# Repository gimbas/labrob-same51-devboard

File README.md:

# SAME51-DevBoard

small and simple development board for the same51 mcus

## Built With

* eagle cad

## Contributing

Currently not looking for external contributers.

Please read [CONTRIBUTING.md](//) for details on our code of conduct, and the process for submitting pull requests to us.

## Authors

* **Rafael Silva** - *initial work* - [gimbas](https://github.com/gimbas)

See also the list of [contributors](https://github.com/gimbas/labrob-same51-devboard/graphs/contributors) who participated in this project.

## License

This project is licensed under the CC 3.0 License - see the [LICENSE.md](LICENSE.md) file for details

## Acknowledgments

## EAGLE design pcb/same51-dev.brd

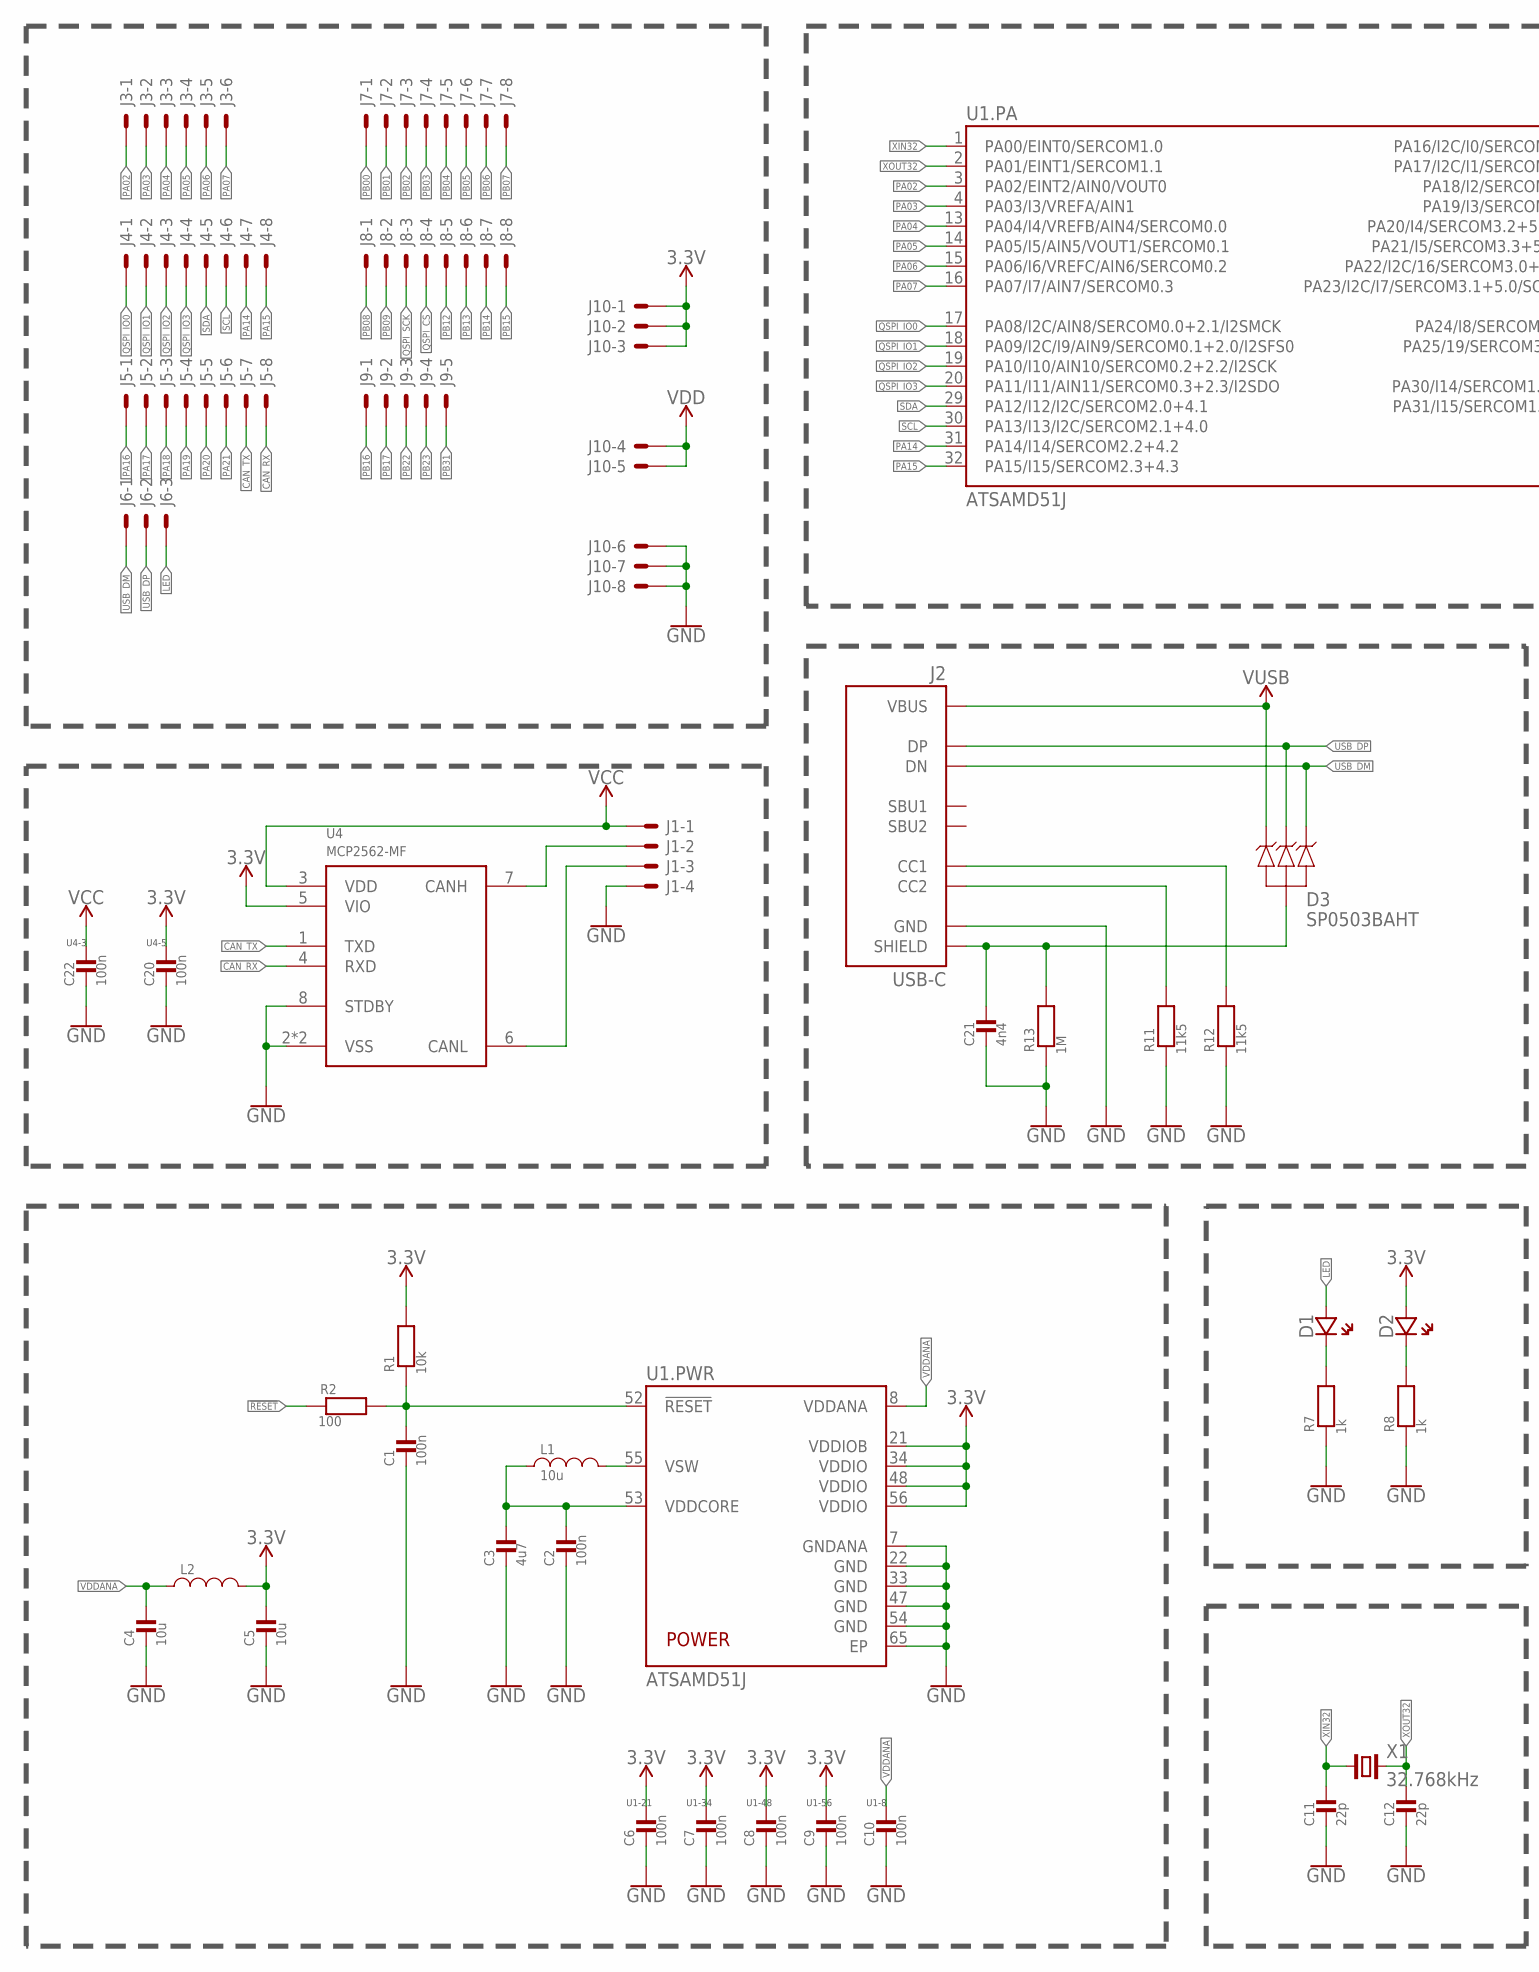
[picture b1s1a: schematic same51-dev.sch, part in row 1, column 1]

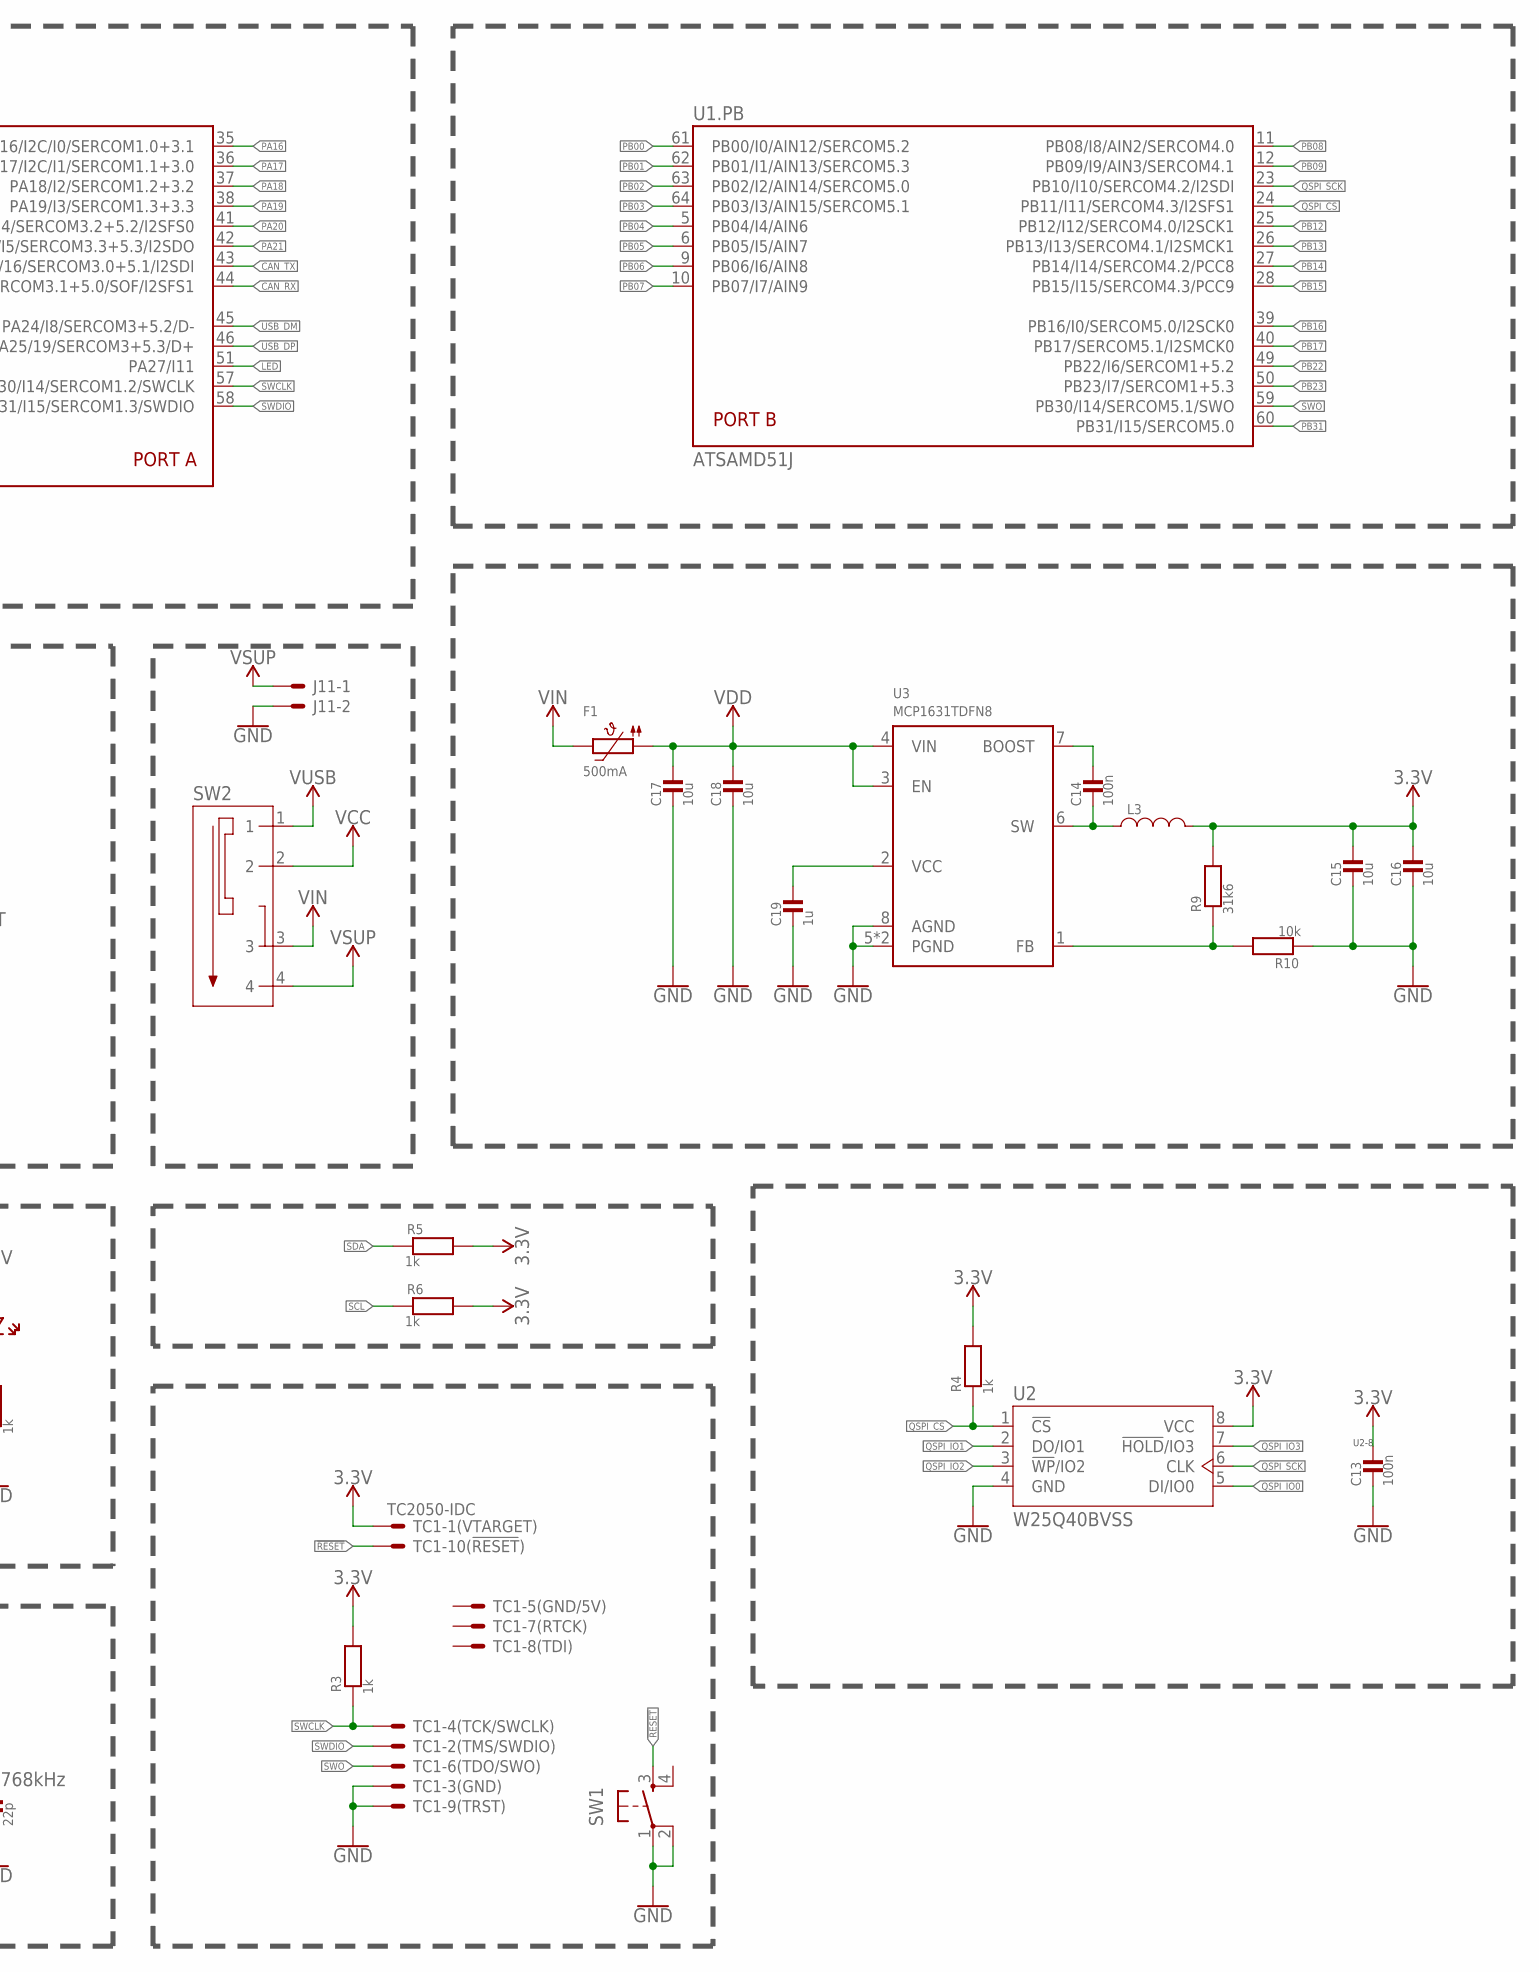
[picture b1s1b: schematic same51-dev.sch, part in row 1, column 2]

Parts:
C1, C2, C6, C7, C8, C9, C10, C13, C14, C20, C22: 100n; 0603_WAVE
C3: 4u7; 0603_WAVE
C4, C5, C15, C16, C17, C18: 10u; 0603_WAVE
C11, C12: 22p; 0603_WAVE
C19: 1u; 0603_WAVE
C21: 4n4; 0603_WAVE
D1, D2: LED0603; CHIPLED_0603
D3: SP0503BAHT; SOT143
F1: 500mA; 0805
J1: 4; 1X4_2.54
J2: USB-C
J3: 6; 1X6_2.54
J4, J5, J7, J8, J10: 8; 1X8_2.54
J6: 3; 1X3_2.54
J9: 5; 1X5_2.54
J11: 2; 2X1_2.54
L1: 10u; _0806
L2: INDUCTOR_NC_0603; _0603
L3: INDUCTOR_NC_0806; _0806
R1, R10: 10k; 0603_WAVE
R2: 100; 0603_WAVE
R3, R4, R5, R6, R7, R8: 1k; 0603_WAVE
R9: 31k6; 0603_WAVE
R11, R12: 11k5; 0603_WAVE
R13: 1M; 0603_WAVE
SW1: PUSH_BUTTON3X4X2; 3X4X2
SW2: MSK-13C01
TC1: TC2050-IDC
U1: ATSAMD51J; VQFN64
U2: W25Q40BVSS; SO08-SS
U3: MCP1631TDFN8; TDFN8
U4: MCP2562-MF; DFN8
X1: 32.768kHz; 2-SMD-3215

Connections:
3.3V: C5.P$1, C6.P$1, C7.P$1, C8.P$1, C9.P$1, C13.P$1, C15.P$1, C16.P$1, C20.P$1, D2.A (AN), J10.1, J10.2, J10.3, L2.2, L3.2, R1.P$2, R3.P$2, R4.P$2, R5.P$2, R6.P$2, R9.P$2, TC1.1, U1.21 (VDDIOB), U1.34 (VDDIO), U1.48 (VDDIO), U1.56 (VDDIO), U2.8 (VCC), U4.5 (VIO)
!RESET: R2.P$1, SW1.3 (4), TC1.10
CAN_RX: J5.8, U1.44 (PA23/I2C/I7/SERCOM3.1+5.0/SOF/I2SFS1), U4.4 (RXD)
CAN_TX: J5.7, U1.43 (PA22/I2C/16/SERCOM3.0+5.1/I2SDI), U4.1 (TXD)
GND: C1.P$2, C2.P$2, C3.P$2, C4.P$2, C5.P$2, C6.P$2, C7.P$2, C8.P$2, C9.P$2, C10.P$2, C11.P$2, C12.P$2, C13.P$2, C15.P$2, C16.P$2, C17.P$2, C18.P$2, C19.P$2, C20.P$2, C21.P$2, C22.P$2, J1.4, J2.A1/B12 (GND), J2.B1/A12 (GND), J10.6, J10.7, J10.8, J11.2, R7.P$1, R8.P$1, R10.P$1, R11.P$1, R12.P$1, R13.P$1, SW1.1, SW1.2, TC1.3, TC1.9, U1.7 (GNDANA), U1.22 (GND), U1.33 (GND), U1.47 (GND), U1.54 (GND), U1.65 (EP), U2.4 (GND), U3.5 (PGND), U3.8 (AGND), U3.9 (PGND), U4.2 (VSS), U4.8 (STDBY), U4.9 (VSS)
LED: D1.A (AN), J6.3, U1.51 (PA27/I11)
unnamed: C1.P$1, R1.P$1, R2.P$2, U1.52 (!RESET)
unnamed: L1.2, U1.55 (VSW)
unnamed: C2.P$1, C3.P$1, L1.1, U1.53 (VDDCORE)
unnamed: C14.P$1, U3.7 (BOOST)
unnamed: C14.P$2, L3.1, U3.6 (SW)
unnamed: R9.P$1, R10.P$2, U3.1 (FB)
unnamed: C19.P$1, U3.2 (VCC)
unnamed: J1.3, U4.6 (CANL)
unnamed: J1.2, U4.7 (CANH)
unnamed: D1.C (CA), R7.P$2
unnamed: C21.P$1, D3.1, J2.SHIELD0 (SHIELD), J2.SHIELD1 (SHIELD), J2.SHIELD2 (SHIELD), J2.SHIELD3 (SHIELD), R13.P$2
unnamed: J2.B5 (CC2), R11.P$2
unnamed: J2.A5 (CC1), R12.P$2
unnamed: D2.C (CA), R8.P$2
PA02: J3.1, U1.3 (PA02/EINT2/AIN0/VOUT0)
PA03: J3.2, U1.4 (PA03/I3/VREFA/AIN1)
PA04: J3.3, U1.13 (PA04/I4/VREFB/AIN4/SERCOM0.0)
PA05: J3.4, U1.14 (PA05/I5/AIN5/VOUT1/SERCOM0.1)
PA06: J3.5, U1.15 (PA06/I6/VREFC/AIN6/SERCOM0.2)
PA07: J3.6, U1.16 (PA07/I7/AIN7/SERCOM0.3)
PA14: J4.7, U1.31 (PA14/I14/SERCOM2.2+4.2)
PA15: J4.8, U1.32 (PA15/I15/SERCOM2.3+4.3)
PA16: J5.1, U1.35 (PA16/I2C/I0/SERCOM1.0+3.1)
PA17: J5.2, U1.36 (PA17/I2C/I1/SERCOM1.1+3.0)
PA18: J5.3, U1.37 (PA18/I2/SERCOM1.2+3.2)
PA19: J5.4, U1.38 (PA19/I3/SERCOM1.3+3.3)
PA20: J5.5, U1.41 (PA20/I4/SERCOM3.2+5.2/I2SFS0)
PA21: J5.6, U1.42 (PA21/I5/SERCOM3.3+5.3/I2SDO)
PB00: J7.1, U1.61 (PB00/I0/AIN12/SERCOM5.2)
PB01: J7.2, U1.62 (PB01/I1/AIN13/SERCOM5.3)
PB02: J7.3, U1.63 (PB02/I2/AIN14/SERCOM5.0)
PB03: J7.4, U1.64 (PB03/I3/AIN15/SERCOM5.1)
PB04: J7.5, U1.5 (PB04/I4/AIN6)
PB05: J7.6, U1.6 (PB05/I5/AIN7)
PB06: J7.7, U1.9 (PB06/I6/AIN8)
PB07: J7.8, U1.10 (PB07/I7/AIN9)
PB08: J8.1, U1.11 (PB08/I8/AIN2/SERCOM4.0)
PB09: J8.2, U1.12 (PB09/I9/AIN3/SERCOM4.1)
PB12: J8.5, U1.25 (PB12/I12/SERCOM4.0/I2SCK1)
PB13: J8.6, U1.26 (PB13/I13/SERCOM4.1/I2SMCK1)
PB14: J8.7, U1.27 (PB14/I14/SERCOM4.2/PCC8)
PB15: J8.8, U1.28 (PB15/I15/SERCOM4.3/PCC9)
PB16: J9.1, U1.39 (PB16/I0/SERCOM5.0/I2SCK0)
PB17: J9.2, U1.40 (PB17/SERCOM5.1/I2SMCK0)
PB22: J9.3, U1.49 (PB22/I6/SERCOM1+5.2)
PB23: J9.4, U1.50 (PB23/I7/SERCOM1+5.3)
PB31: J9.5, U1.60 (PB31/I15/SERCOM5.0)
QSPI_CS: J8.4, R4.P$1, U1.24 (PB11/I11/SERCOM4.3/I2SFS1), U2.1 (!CS!)
QSPI_IO0: J4.1, U1.17 (PA08/I2C/AIN8/SERCOM0.0+2.1/I2SMCK), U2.5 (DI/IO0)
QSPI_IO1: J4.2, U1.18 (PA09/I2C/I9/AIN9/SERCOM0.1+2.0/I2SFS0), U2.2 (DO/IO1)
QSPI_IO2: J4.3, U1.19 (PA10/I10/AIN10/SERCOM0.2+2.2/I2SCK), U2.3 (!WP!/IO2)
QSPI_IO3: J4.4, U1.20 (PA11/I11/AIN11/SERCOM0.3+2.3/I2SDO), U2.7 (!HOLD!/IO3)
QSPI_SCK: J8.3, U1.23 (PB10/I10/SERCOM4.2/I2SDI), U2.6 (CLK)
SCL: J4.6, R6.P$1, U1.30 (PA13/I13/I2C/SERCOM2.1+4.0)
SDA: J4.5, R5.P$1, U1.29 (PA12/I12/I2C/SERCOM2.0+4.1)
SWCLK: R3.P$1, TC1.4, U1.57 (PA30/I14/SERCOM1.2/SWCLK)
SWDIO: TC1.2, U1.58 (PA31/I15/SERCOM1.3/SWDIO)
SWO: TC1.6, U1.59 (PB30/I14/SERCOM5.1/SWO)
USB_DM: D3.4, J2.A7 (DN), J2.B7 (DN), J6.1, U1.45 (PA24/I8/SERCOM3+5.2/D-)
USB_DP: D3.3, J2.A6 (DP), J2.B6 (DP), J6.2, U1.46 (PA25/19/SERCOM3+5.3/D+)
VCC: C22.P$1, J1.1, SW2.2, U4.3 (VDD)
VDD: C17.P$1, C18.P$1, F1.1, J10.4, J10.5, U3.3 (EN), U3.4 (VIN)
VDDANA: C4.P$1, C10.P$1, L2.1, U1.8 (VDDANA)
VIN: F1.2, SW2.3
VSUP: J11.1, SW2.4
VUSB: D3.2, J2.A4/B9 (VBUS), J2.B4/A9 (VBUS), SW2.1
XIN32: C11.P$1, U1.1 (PA00/EINT0/SERCOM1.0), X1.1
XOUT32: C12.P$1, U1.2 (PA01/EINT1/SERCOM1.1), X1.2

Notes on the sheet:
U1-21
U1-34
U1-48
U1-56
U1-8
U2-8
U4-5
U4-3

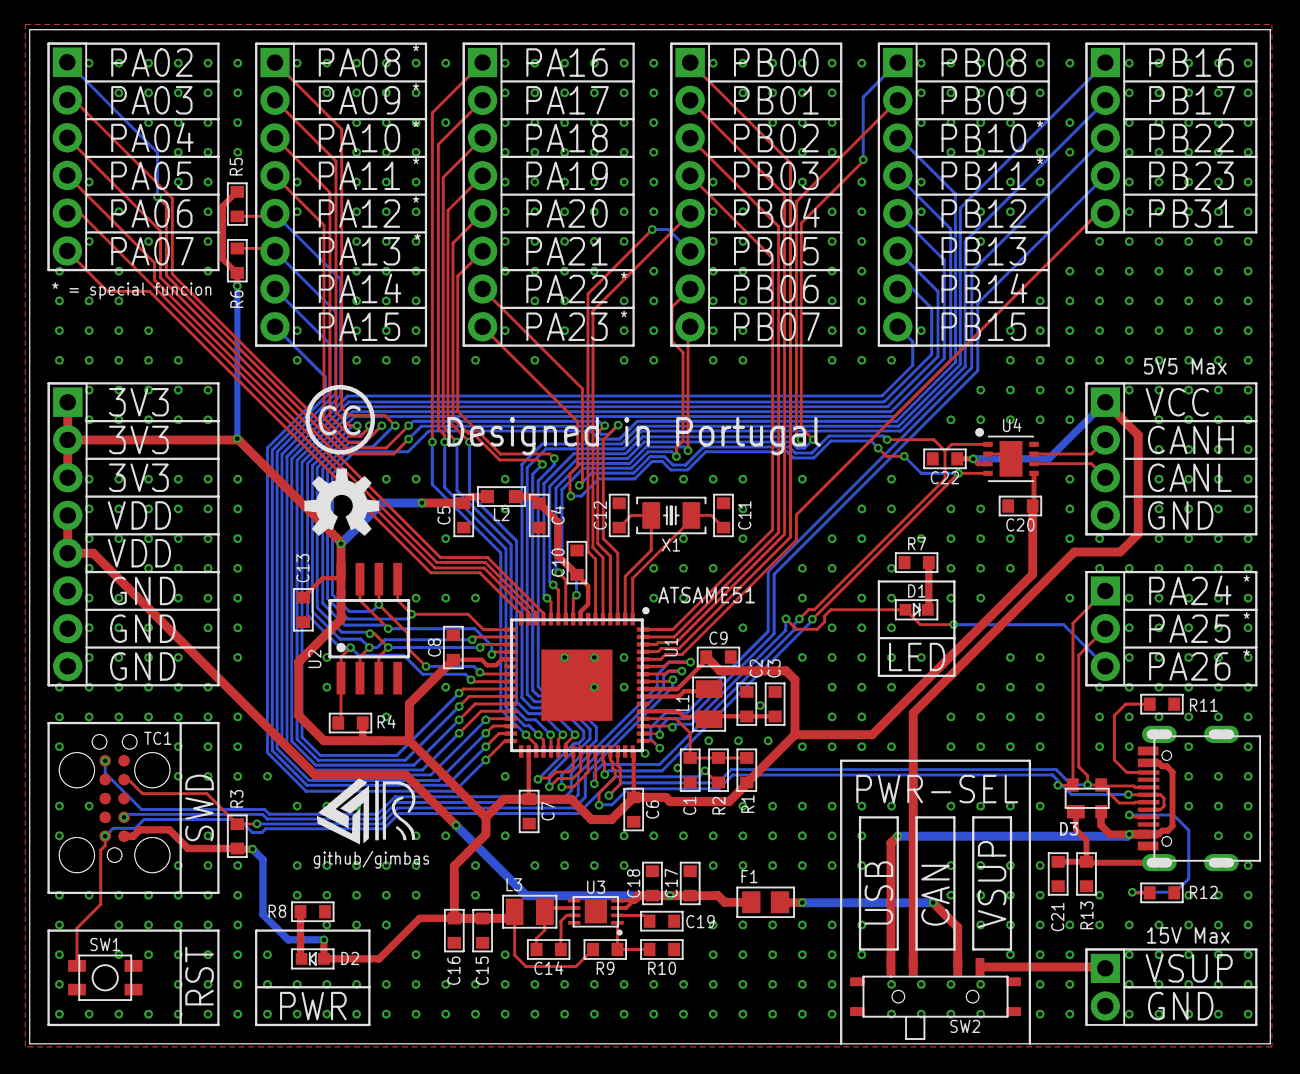
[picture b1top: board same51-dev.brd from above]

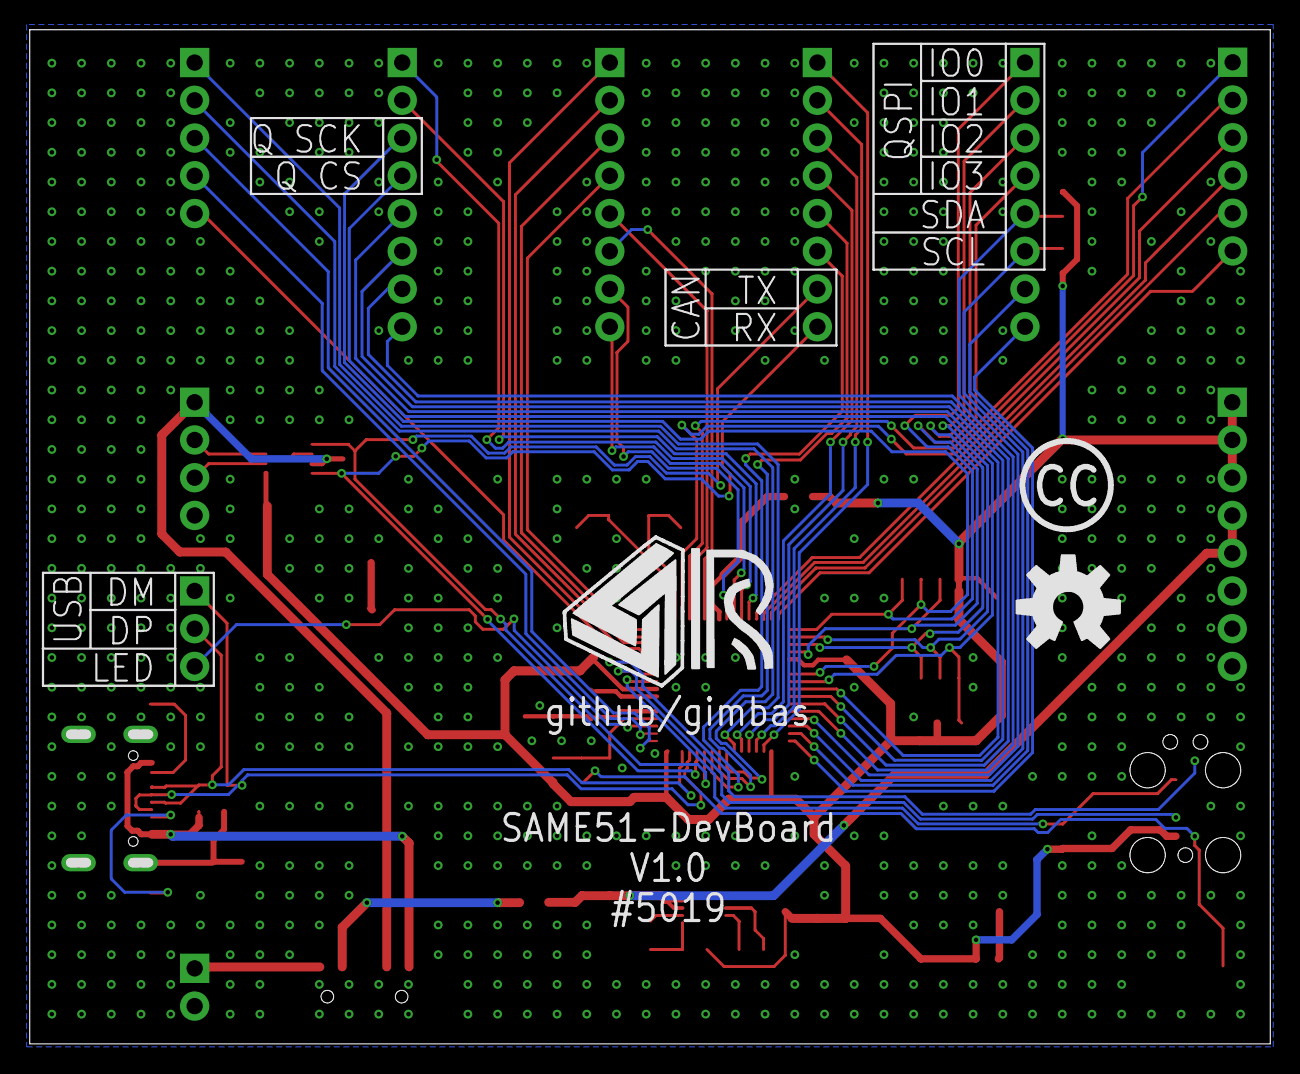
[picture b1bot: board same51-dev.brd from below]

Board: 2 copper layers, 82.8 x 67.6 mm, 65 parts (2 on the bottom side), 74 nets.

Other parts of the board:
U$1: OSHW-LOGO-L
U$2: RAFAEL_SILVA_10MM_ALT
U$3: RAFAEL_SILVA_5MM_ALT_3
U$4: OSHW-LOGO-M

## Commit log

2019-12-09 sch work
2019-12-09 finished sch, started pcb
2019-12-11 power routing
2019-12-11 finished signal routing
2019-12-12 V1.0 Ready for production
2019-12-14 added README and LICENSE

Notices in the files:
pcb/same51-dev.sch:
LICENSE: Licensed under Creative Commons Attribution-ShareAlike 3.0 Unported
